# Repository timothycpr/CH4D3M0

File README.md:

# Focus_CHAdeMO

The software and information provided here relates to hazardous and potentially deadly uses. EV batteries and DC chargers can produce hundreds of Amps of current at more than 1000 Volts, which can literally vaporise body parts. As wiser man said "Not only will this kill you, it will hurt the whole time you're dying"

Anyone that utiizes this infomration/code must assume full responsibility for their actions and ensure prudent & safe operation. While good faith effort has been made to implement safety checks and fail-safes in code and hardware, I can in no way guarantee that using this is safe.

Similarly, modification of an EV to add after-market fast charging creates the same risks to people and property. Anyone implemeting any of these methods must assume full responsibility for their actions.

I will not be held liable for the actions of others relating to any use of this code, information or hardware.

With great power comes great responsibility - and 30-50kW is a *lot* of power.

-----------

Software and hardware specs to implement CHAdeMO fast charging on early model Ford Focus EVs

This hardware and software was originally developed and implemented by "Sefs" of the MyFocusElectic forums - building a home fast charger and a means to interface it with his vehicle.

After moving on to a Model 3 with much better range, the hardware was stripped from his 2012 Focus and eventually ended up in my 2012 Focus.

This project has two primary systems - the vehicle CHAdeMO interface and the charger-side management system.

In the vehicle CHAdeMO interface, an EVTV Due is spliced into the vehicle CANBus to send/receive/process CAN data frames. The data pins from the CHAdeMO plug are routed through a separate CANBus transceiver that converts them to a TTL data stream that is fed into the EVTV Due.

Data from these two systems is then used to control a CHAdeMO charging session, ultimately connecting the vehicle HVDC bus to that of the charger.

In total, the connection requires the following physical hardware:

  1 EVTV Due (http://store.evtv.me/proddetail.php?prod=EVTVDue2) ARM-based microcontroller with CAN Tranceiver

  1 EVAL-ADM3052EBZ (https://www.digikey.com/en/products/detail/analog-devices-inc/EVAL-ADM3052EBZ/2709315) Isolated CAN Transceiver

  1 HL-52S (https://www.newegg.com/p/285-0018-000E9?item=9SIA4W246U6059) Inverting Optocoupled 5V relays

  ~~1 PST-DC2012 (https://www.powerstream.com/DC3611.htm) or similarly capable, Fully Isolated DC/DC Converter with 12V output. (Original supply board was marked with a 5V model number - PST-DC2405 - but tested as 12V out)~~
  Using a double pole relay, one can switch the contactors to the vehicle 12V rather than driving them from a power supply on this board.

  1 12V SPDT relay and socket/harness (https://www.summitracing.com/parts/via-80237)

  2 3.3V optoisolators with breakouts (https://www.sparkfun.com/products/9118)

  2 Gigavac GX14BA Sealed Contactors (350A) (https://octopart.com/gx14ba-gigavac-24213166) 12V HVDC Normally open contactors

  1 CHAdeMO inlet (https://shop.quickchargepower.com/CHAdeMO-Inlets-YazInlet.htm) with harness

  1 Optional USB passthrough connector and USB A (host) to USB B (client)

  Resistors: +/-5%; 100 Ohm, 200 Ohm, 1 KOhm, two 15 KOhm.

After validating operation, all components have been consolidated onto a single shield, minus the HVDC contactors themselves. Components for re-inverting f/g/d1/d2 have been omitted and negated in code.

In addition to those signal path components, the following physical components are utilized

  1 plastic project box with grid insert

  1 replacement TCM cover (passthrough for HVDC wiring)

  6 crimp fit ring terminals ("Cable lugs"), 6 weatherproof passthroughs

  2 8-position terminal blocks

  1 7-wire weatherproof passthrough for CHAdeMO signal wiring

  1 4-wire or 2 2-wire weatherproof passthroughs for 12V/Ground/CANH/CANL

  ~30 crimp on fork terminals

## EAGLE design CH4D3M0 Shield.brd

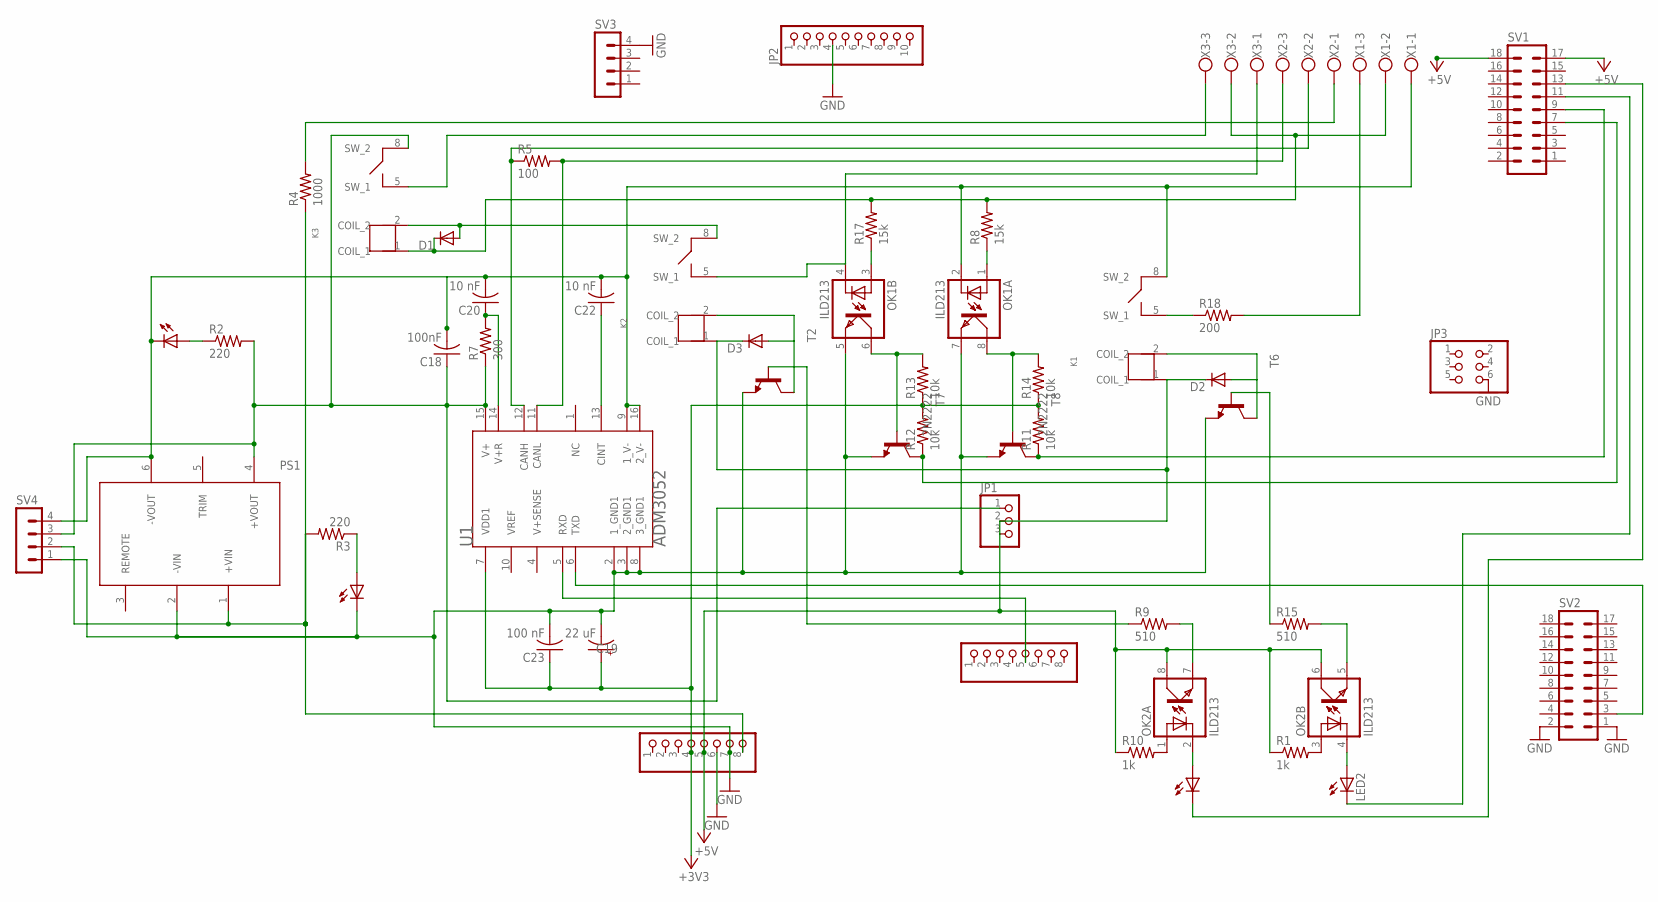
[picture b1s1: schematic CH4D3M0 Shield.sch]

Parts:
ADCH, ADCH2: PINHD-1X8; 1X08
C18: 100nF; C025-024X044
C19: 22 uF; E2,5RE
C20, C22: 10 nF; C025-024X044
C23: 100 nF; C025-024X044
D1, D2, D3: DIODE-D-5; D-5
JP1: PINHD-1X3; 1X03
JP2: PINHD-1X10; 1X10
JP3: PINHD-2X3; 2X03
K1, K2, K3: G6DN-1ATHROUGH_HOLE; G6DN-1A
LED1, LED2, LED3, LED4: LED_ELD260; LED_LD260
OK1, OK2: ILD213; SOIC08
PS1: JCMXXTHROUGH_HOLE; JCMXX
R1, R10: 1k; 0204/7
R2, R3: 220; 0204/7
R4: 1000; 0204/7
R5: 100; 0204/7
R7: 300; 0204/7
R8, R17: 15k; 0204/7
R9, R15: 510; 0204/7
R11, R12, R13, R14: 10k; 0204/7
R18: 200; 0204/7
SV1, SV2: MA09-2
SV3, SV4: MA04-1
T2, T6: BC547-NPN-TO92-CBE; TO92-CBE
T7, T8: 2N2222; TO92-EBC-OVAL
U1: ANALOG_DEVICES_INC_ADM3052ANALOG_DEVICES_INC_ADM3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; ANALOG_DEVICES_INC_ADM3052_0
X1, X2, X3: W237-103

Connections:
+3V3: ADCH2.4, C19.+, C23.1, R11.2, R12.2, R13.1, R14.1, U1.7 (VDD1)
+5V: ADCH2.5, D2.C, D3.C, JP1.2, JP1.3, K1.1 (COIL_1), K2.1 (COIL_1), OK2.6 (COL), OK2.8 (COL), R1.1, R10.1, SV1.17, SV1.18
CAN_HIGH_DBLUE: R5.1, U1.12 (CANH), X2.2
CAN_LOW_GREEN: R5.2, U1.11 (CANL), X2.3
CINH_LBLUE: R18.2, X1.3
CNTF_YELLOW: R4.2, X2.1
CONTACTOR_NEG: D1.C, K3.1 (COIL_1), R8.2, R17.2, X1.2, X3.2
CONTACTOR_POS: K3.5 (SW_1), X3.3
D1_F: R11.1, SV1.9, T8.C
D2_G: R12.1, SV1.7, T7.C
GND: ADCH2.6, ADCH2.7, C19.-, C23.2, JP2.4, JP3.6, LED4.K (C), OK1.5 (EMIT), OK1.7 (EMIT), PS1.2 (-VIN), SV2.1, SV2.2, SV3.4, SV4.1, T2.E, T6.E, T7.E, T8.E, U1.2 (1_GND1), U1.3 (2_GND1), U1.8 (3_GND1)
HGND: C18.2, C20.2, C22.2, K1.8 (SW_2), LED3.K (C), OK1.2 (C), PS1.6 (-VOUT), SV4.4, U1.9 (1_V-), U1.16 (2_V-), X1.1
unnamed: C18.1, JP1.1, K3.8 (SW_2), PS1.4 (+VOUT), R2.2, R7.1, SV4.3, U1.15 (V+)
unnamed: C20.1, R7.2, U1.14 (V+R)
unnamed: C22.1, U1.13 (CINT)
unnamed: ADCH2.8, PS1.1 (+VIN), R3.2, R4.1, SV4.2
unnamed: ADCH.5, U1.5 (RXD)
unnamed: K1.5 (SW_1), R18.1
unnamed: OK1.1 (A), R8.1
unnamed: OK1.3 (A), R17.1
unnamed: D1.A, K2.8 (SW_2), K3.2 (COIL_2)
unnamed: OK1.6 (COL), R13.2, T7.B
unnamed: OK1.8 (COL), R14.2, T8.B
unnamed: SV2.3, U1.6 (TXD)
unnamed: D2.A, K1.2 (COIL_2), T6.C
unnamed: D3.A, K2.2 (COIL_2), T2.C
unnamed: OK2.7 (EMIT), R9.2
unnamed: LED1.A, OK2.2 (C)
unnamed: OK2.1 (A), R10.2
unnamed: OK2.3 (A), R1.2
unnamed: R9.1, T2.B
unnamed: LED1.K (C), SV1.13
unnamed: R15.1, T6.B
unnamed: OK2.5 (EMIT), R15.2
unnamed: LED2.A, OK2.4 (C)
unnamed: LED2.K (C), SV1.11
unnamed: LED3.A, R2.1
unnamed: LED4.A, R3.1
S2_10_WHITE: K2.5 (SW_1), OK1.4 (C), X3.1

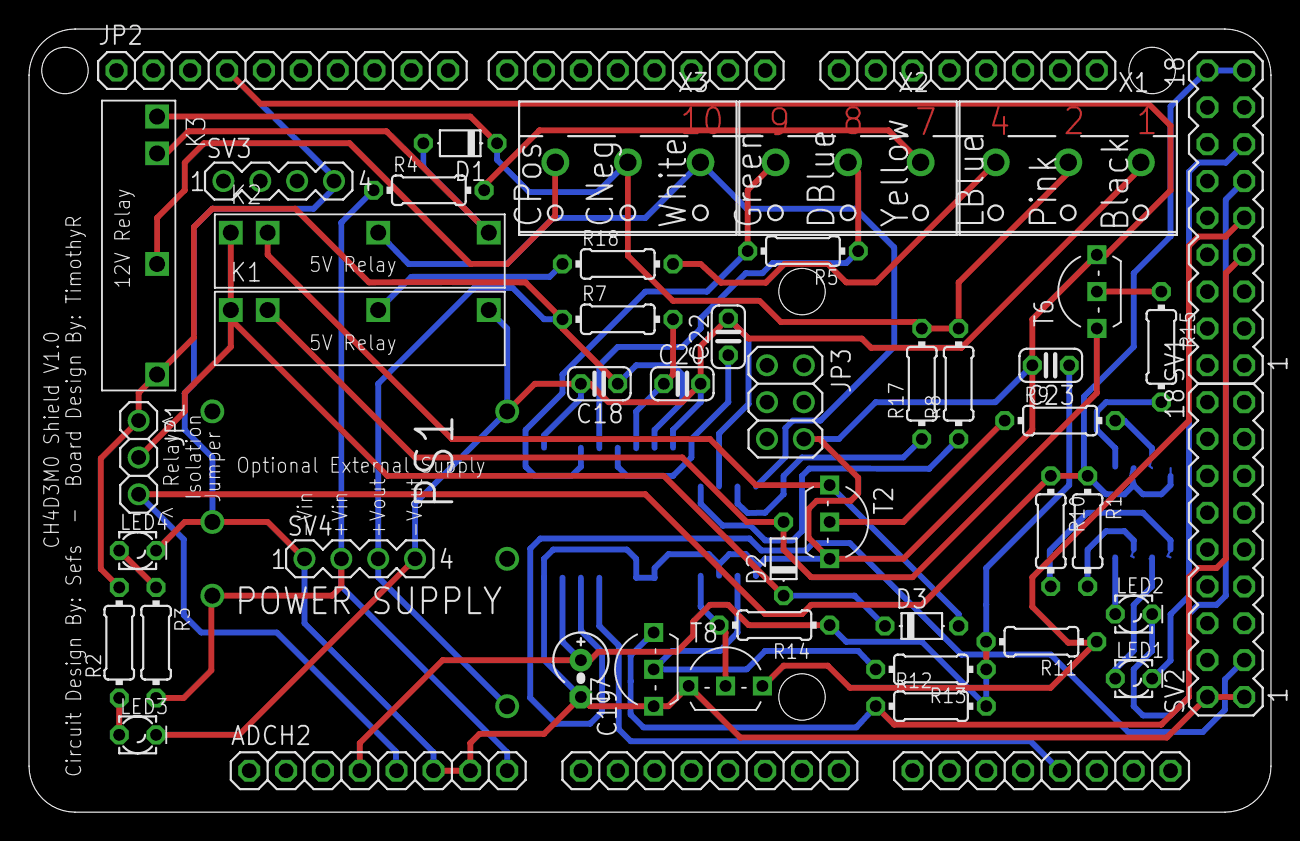
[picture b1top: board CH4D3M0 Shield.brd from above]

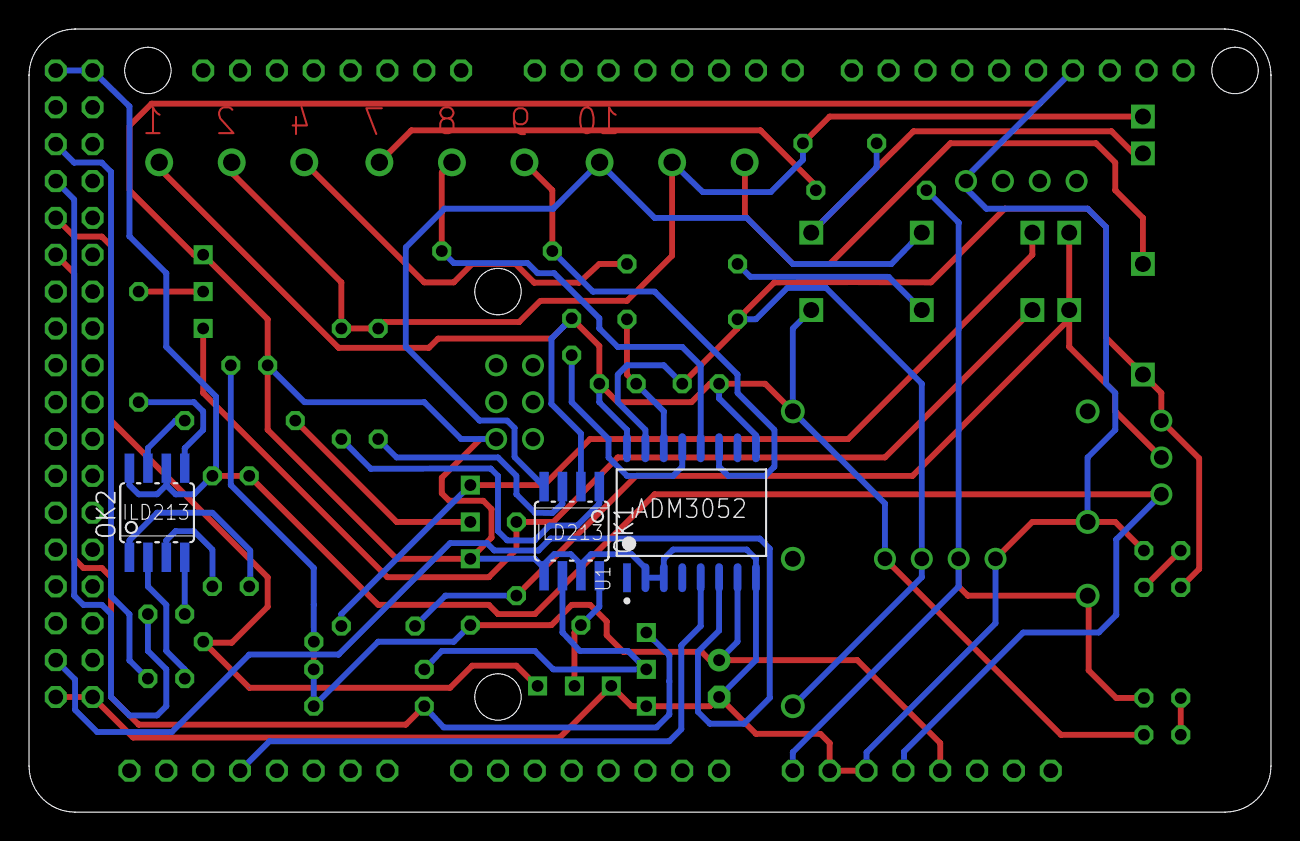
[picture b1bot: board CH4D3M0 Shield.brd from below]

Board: 2 copper layers, 85.6 x 54.0 mm, 54 parts (3 on the bottom side), 39 nets.

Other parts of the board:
ADCL: 1X08
COMMUNICATION: 1X08
PWML: 1X08

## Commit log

2024-10-16 Create README.md
    Moving to public repository
2024-10-16 Update README.md
    Adding line breaks to properly separate list items
2024-10-16 Add files via upload
    Annotated schematic of charger and vehicle CHAdeMO interfaces
2024-10-18 Add files via upload
    Initial version of the shield board. Current power supply is incorrect
2024-10-18 Add files via upload
    Tweaks of schematic - need to validate the resistor values
2024-10-18 Add files via upload
    Need to doublecheck all the read and write logic to make sure nothing is incorrectly inverted for the current circuit.
2024-10-18 Add files via upload
    App to monitor and display vehicle data during charging or operation. Appears to no longer work correctly in Windows 10.
2024-10-18 Add files via upload
    Higher res
2024-10-18 Add files via upload
    Not sure why Github isn't letting me update the existing file, so here's another I guess
2024-10-19 Update README.md
    Correcting power supply model number
2024-10-19 Update README.md
    Corrected contactor part number, fixed dead link
2024-12-11 Add files via upload
    Initial upload of Arduino Due sketch. Work in progress, use at your own risk.
2024-12-11 Delete CH4D3M0_Shield_V1.ino
    Replaced with header'd version
2024-12-25 Update CH4D3M0_Shield.ino
    Updating comments
